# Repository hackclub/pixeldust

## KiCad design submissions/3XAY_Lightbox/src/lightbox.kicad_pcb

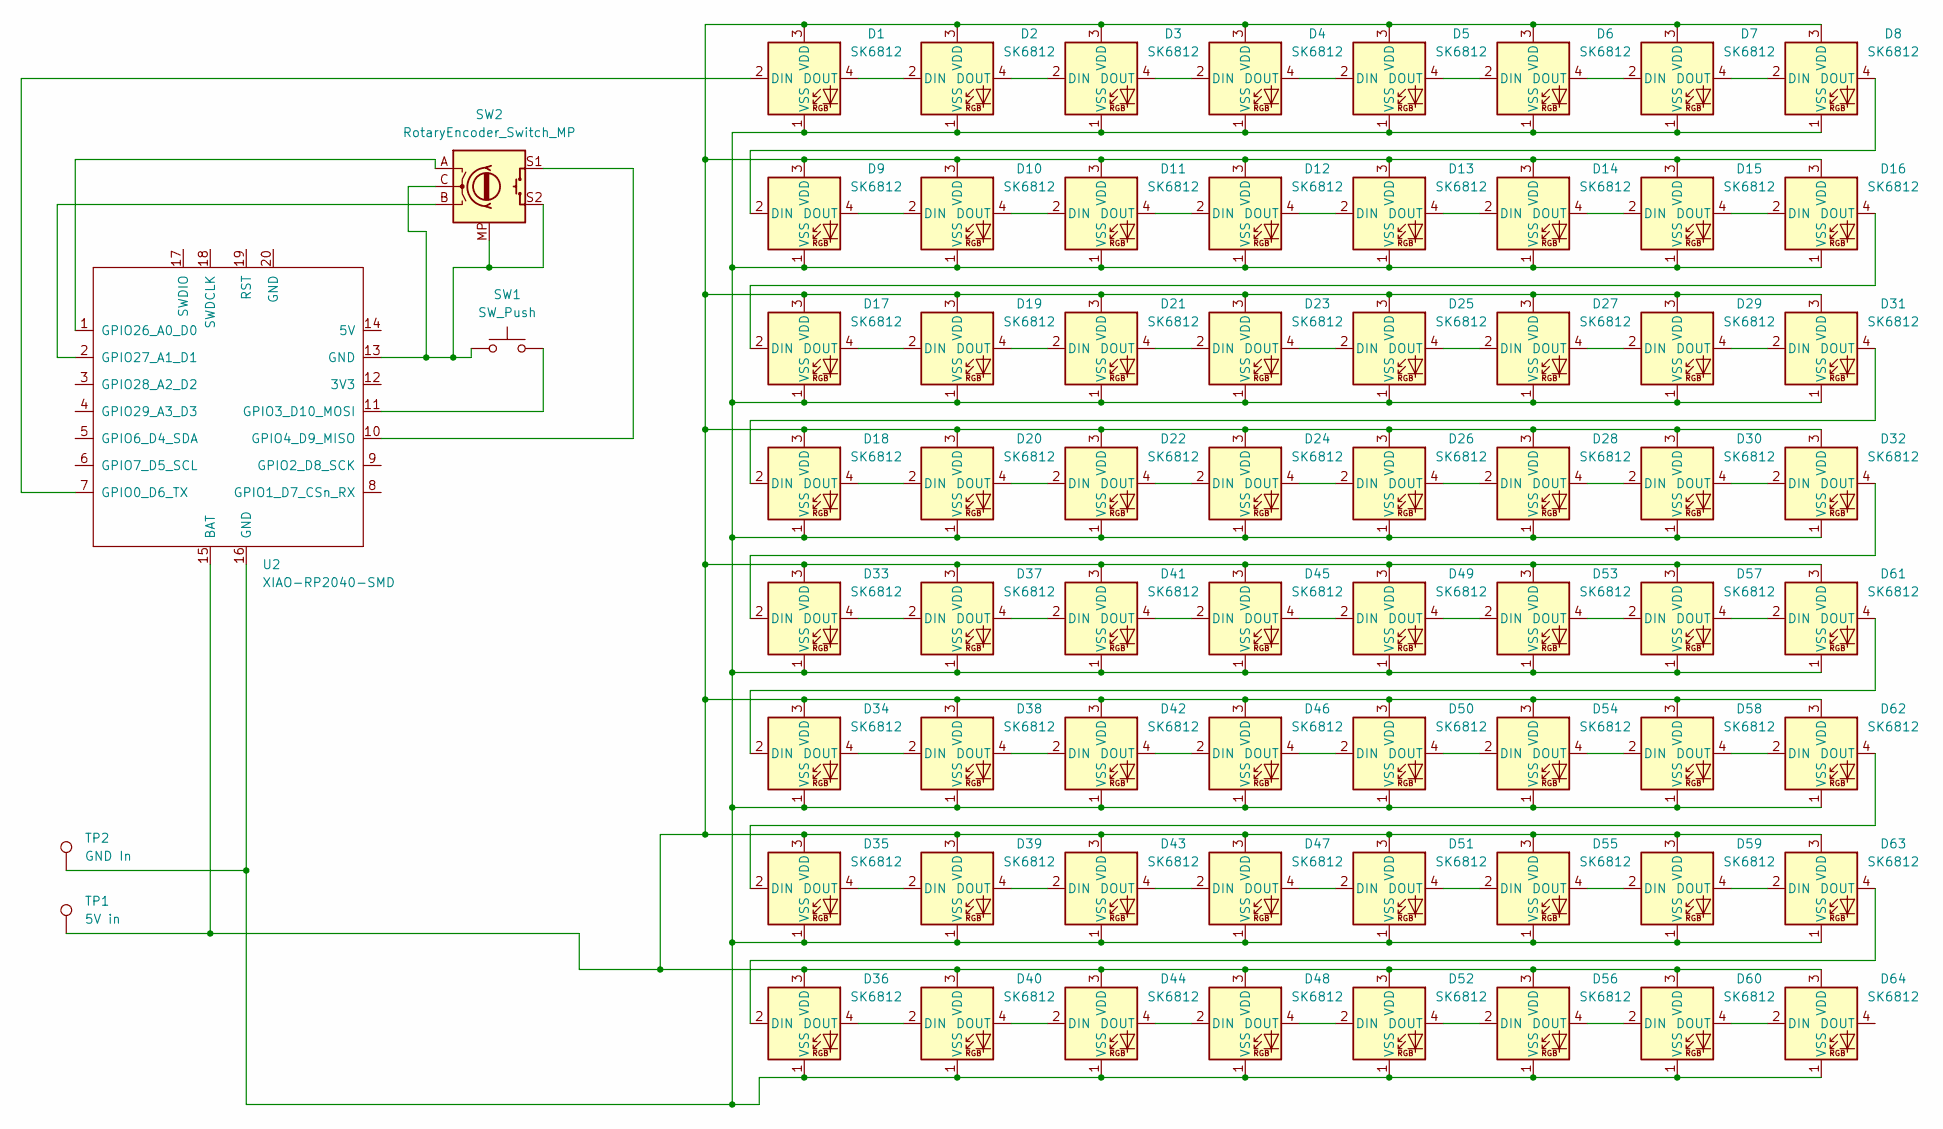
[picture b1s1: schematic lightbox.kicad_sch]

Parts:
D1, D2, D3, D4, D5, D6, D7, D8, D9, D10, D11, D12, D13, D14, D15, D16, D17, D18, D19, D20, D21, D22, D23, D24, D25, D26, D27, D28, D29, D30, D31, D32, D33, D34, D35, D36, D37, D38, D39, D40, D41, D42, D43, D44, D45, D46, D47, D48, D49, D50, D51, D52, D53, D54, D55, D56, D57, D58, D59, D60, D61, D62, D63, D64: SK6812; LED_SK6812_PLCC4_5.0x5.0mm_P3.2mm
SW1: SW_Push; SW_Cherry_MX_1.00u_PCB
SW2: RotaryEncoder_Switch_MP; RotaryEncoder_Alps_EC11E-Switch_Vertical_H20mm
TP1: 5V in; TestPoint_Pad_D3.0mm
TP2: GND In; TestPoint_Pad_D3.0mm
U2: XIAO-RP2040-SMD

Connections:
unnamed: D1.2 (DIN), U2.7 (GPIO0_D6_TX)
unnamed: D1.4 (DOUT), D2.2 (DIN)
unnamed: D1.3 (VDD), D2.3 (VDD), D3.3 (VDD), D4.3 (VDD), D5.3 (VDD), D6.3 (VDD), D7.3 (VDD), D8.3 (VDD), D9.3 (VDD), D10.3 (VDD), D11.3 (VDD), D12.3 (VDD), D13.3 (VDD), D14.3 (VDD), D15.3 (VDD), D16.3 (VDD), D17.3 (VDD), D18.3 (VDD), D19.3 (VDD), D20.3 (VDD), D21.3 (VDD), D22.3 (VDD), D23.3 (VDD), D24.3 (VDD), D25.3 (VDD), D26.3 (VDD), D27.3 (VDD), D28.3 (VDD), D29.3 (VDD), D30.3 (VDD), D31.3 (VDD), D32.3 (VDD), D33.3 (VDD), D34.3 (VDD), D35.3 (VDD), D36.3 (VDD), D37.3 (VDD), D38.3 (VDD), D39.3 (VDD), D40.3 (VDD), D41.3 (VDD), D42.3 (VDD), D43.3 (VDD), D44.3 (VDD), D45.3 (VDD), D46.3 (VDD), D47.3 (VDD), D48.3 (VDD), D49.3 (VDD), D50.3 (VDD), D51.3 (VDD), D52.3 (VDD), D53.3 (VDD), D54.3 (VDD), D55.3 (VDD), D56.3 (VDD), D57.3 (VDD), D58.3 (VDD), D59.3 (VDD), D60.3 (VDD), D61.3 (VDD), D62.3 (VDD), D63.3 (VDD), D64.3 (VDD), TP1.1, U2.15 (BAT)
unnamed: D1.1 (VSS), D2.1 (VSS), D3.1 (VSS), D4.1 (VSS), D5.1 (VSS), D6.1 (VSS), D7.1 (VSS), D8.1 (VSS), D9.1 (VSS), D10.1 (VSS), D11.1 (VSS), D12.1 (VSS), D13.1 (VSS), D14.1 (VSS), D15.1 (VSS), D16.1 (VSS), D17.1 (VSS), D18.1 (VSS), D19.1 (VSS), D20.1 (VSS), D21.1 (VSS), D22.1 (VSS), D23.1 (VSS), D24.1 (VSS), D25.1 (VSS), D26.1 (VSS), D27.1 (VSS), D28.1 (VSS), D29.1 (VSS), D30.1 (VSS), D31.1 (VSS), D32.1 (VSS), D33.1 (VSS), D34.1 (VSS), D35.1 (VSS), D36.1 (VSS), D37.1 (VSS), D38.1 (VSS), D39.1 (VSS), D40.1 (VSS), D41.1 (VSS), D42.1 (VSS), D43.1 (VSS), D44.1 (VSS), D45.1 (VSS), D46.1 (VSS), D47.1 (VSS), D48.1 (VSS), D49.1 (VSS), D50.1 (VSS), D51.1 (VSS), D52.1 (VSS), D53.1 (VSS), D54.1 (VSS), D55.1 (VSS), D56.1 (VSS), D57.1 (VSS), D58.1 (VSS), D59.1 (VSS), D60.1 (VSS), D61.1 (VSS), D62.1 (VSS), D63.1 (VSS), D64.1 (VSS), TP2.1, U2.16 (GND)
unnamed: D2.4 (DOUT), D3.2 (DIN)
unnamed: D3.4 (DOUT), D4.2 (DIN)
unnamed: D4.4 (DOUT), D5.2 (DIN)
unnamed: D5.4 (DOUT), D6.2 (DIN)
unnamed: D6.4 (DOUT), D7.2 (DIN)
unnamed: D7.4 (DOUT), D8.2 (DIN)
unnamed: D8.4 (DOUT), D9.2 (DIN)
unnamed: D9.4 (DOUT), D10.2 (DIN)
unnamed: D10.4 (DOUT), D11.2 (DIN)
unnamed: D11.4 (DOUT), D12.2 (DIN)
unnamed: D12.4 (DOUT), D13.2 (DIN)
unnamed: D13.4 (DOUT), D14.2 (DIN)
unnamed: D14.4 (DOUT), D15.2 (DIN)
unnamed: D15.4 (DOUT), D16.2 (DIN)
unnamed: D16.4 (DOUT), D17.2 (DIN)
unnamed: D17.4 (DOUT), D19.2 (DIN)
unnamed: D18.2 (DIN), D31.4 (DOUT)
unnamed: D18.4 (DOUT), D20.2 (DIN)
unnamed: D19.4 (DOUT), D21.2 (DIN)
unnamed: D20.4 (DOUT), D22.2 (DIN)
unnamed: D21.4 (DOUT), D23.2 (DIN)
unnamed: D22.4 (DOUT), D24.2 (DIN)
unnamed: D23.4 (DOUT), D25.2 (DIN)
unnamed: D24.4 (DOUT), D26.2 (DIN)
unnamed: D25.4 (DOUT), D27.2 (DIN)
unnamed: D26.4 (DOUT), D28.2 (DIN)
unnamed: D27.4 (DOUT), D29.2 (DIN)
unnamed: D28.4 (DOUT), D30.2 (DIN)
unnamed: D29.4 (DOUT), D31.2 (DIN)
unnamed: D30.4 (DOUT), D32.2 (DIN)
unnamed: D32.4 (DOUT), D33.2 (DIN)
unnamed: D33.4 (DOUT), D37.2 (DIN)
unnamed: D34.2 (DIN), D61.4 (DOUT)
unnamed: D34.4 (DOUT), D38.2 (DIN)
unnamed: D35.2 (DIN), D62.4 (DOUT)
unnamed: D35.4 (DOUT), D39.2 (DIN)
unnamed: D36.2 (DIN), D63.4 (DOUT)
unnamed: D36.4 (DOUT), D40.2 (DIN)
unnamed: D37.4 (DOUT), D41.2 (DIN)
unnamed: D38.4 (DOUT), D42.2 (DIN)
unnamed: D39.4 (DOUT), D43.2 (DIN)
unnamed: D40.4 (DOUT), D44.2 (DIN)
unnamed: D41.4 (DOUT), D45.2 (DIN)
unnamed: D42.4 (DOUT), D46.2 (DIN)
unnamed: D43.4 (DOUT), D47.2 (DIN)
unnamed: D44.4 (DOUT), D48.2 (DIN)
unnamed: D45.4 (DOUT), D49.2 (DIN)
unnamed: D46.4 (DOUT), D50.2 (DIN)
unnamed: D47.4 (DOUT), D51.2 (DIN)
unnamed: D48.4 (DOUT), D52.2 (DIN)
unnamed: D49.4 (DOUT), D53.2 (DIN)
unnamed: D50.4 (DOUT), D54.2 (DIN)
unnamed: D51.4 (DOUT), D55.2 (DIN)
unnamed: D52.4 (DOUT), D56.2 (DIN)
unnamed: D53.4 (DOUT), D57.2 (DIN)
unnamed: D54.4 (DOUT), D58.2 (DIN)
unnamed: D55.4 (DOUT), D59.2 (DIN)
unnamed: D56.4 (DOUT), D60.2 (DIN)
unnamed: D57.4 (DOUT), D61.2 (DIN)
unnamed: D58.4 (DOUT), D62.2 (DIN)
unnamed: D59.4 (DOUT), D63.2 (DIN)
unnamed: D60.4 (DOUT), D64.2 (DIN)
unnamed: SW1.1, SW2.C, SW2.MP, SW2.S2, U2.13 (GND)
unnamed: SW1.2, U2.11 (GPIO3_D10_MOSI)
unnamed: SW2.S1, U2.10 (GPIO4_D9_MISO)
unnamed: SW2.A, U2.1 (GPIO26_A0_D0)
unnamed: SW2.B, U2.2 (GPIO27_A1_D1)

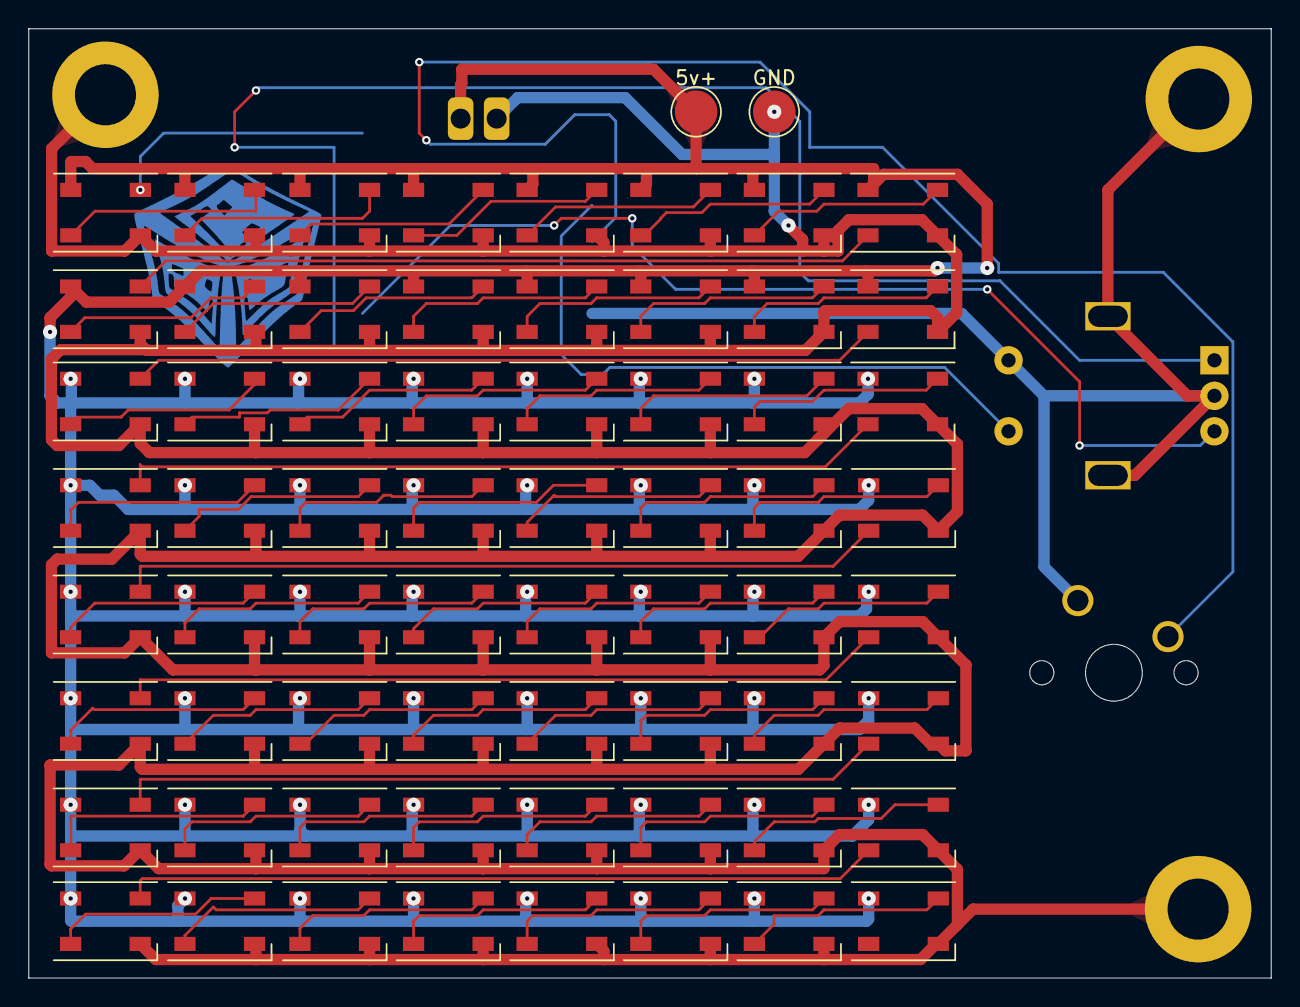
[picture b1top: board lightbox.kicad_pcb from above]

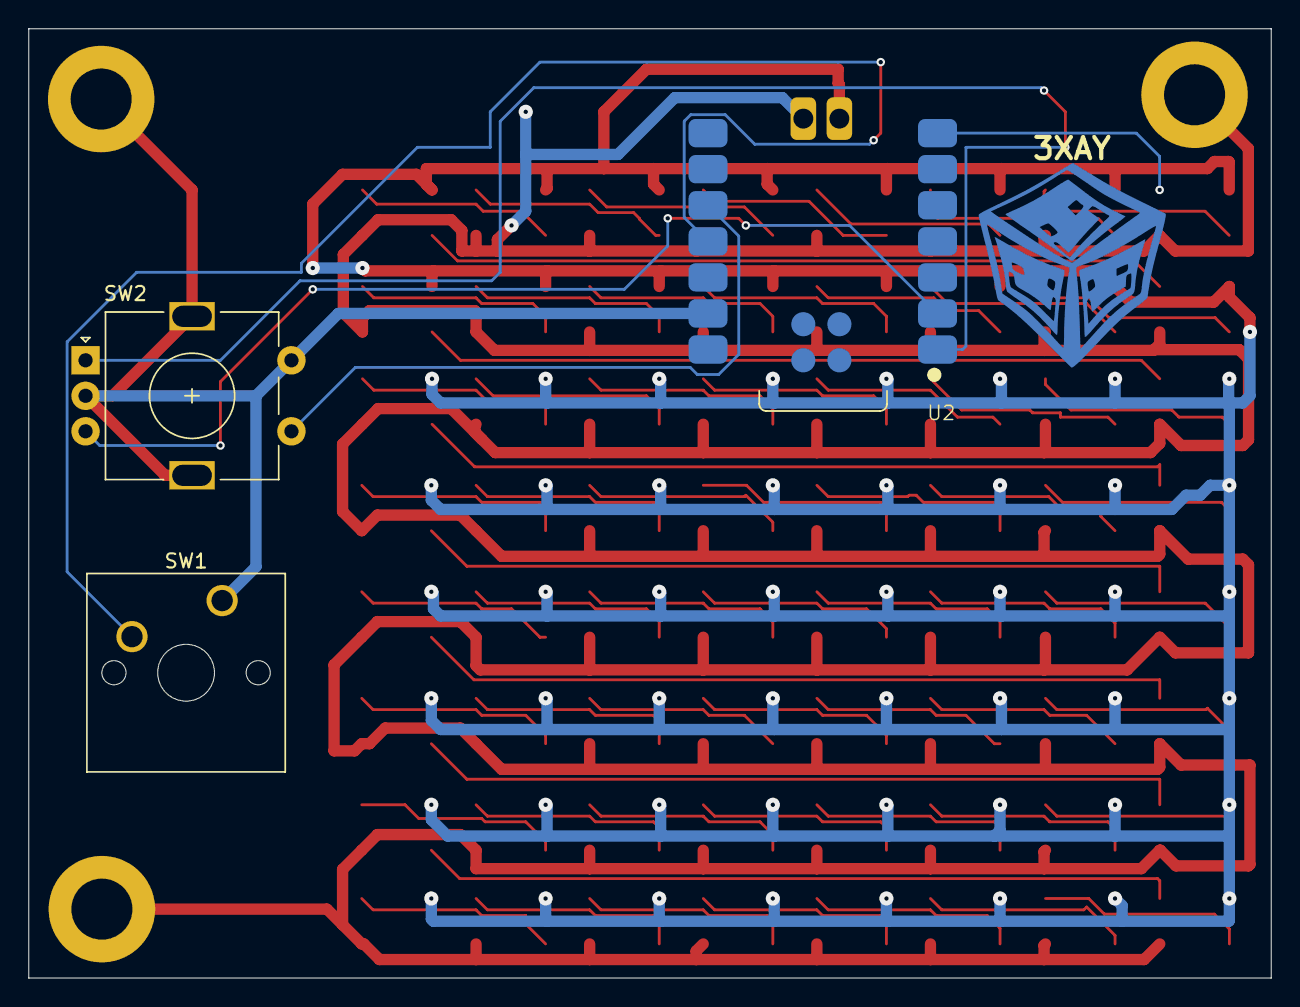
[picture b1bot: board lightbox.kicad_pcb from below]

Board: 2 copper layers, 87.5 x 66.8 mm, 69 parts (3 on the bottom side), 71 nets.

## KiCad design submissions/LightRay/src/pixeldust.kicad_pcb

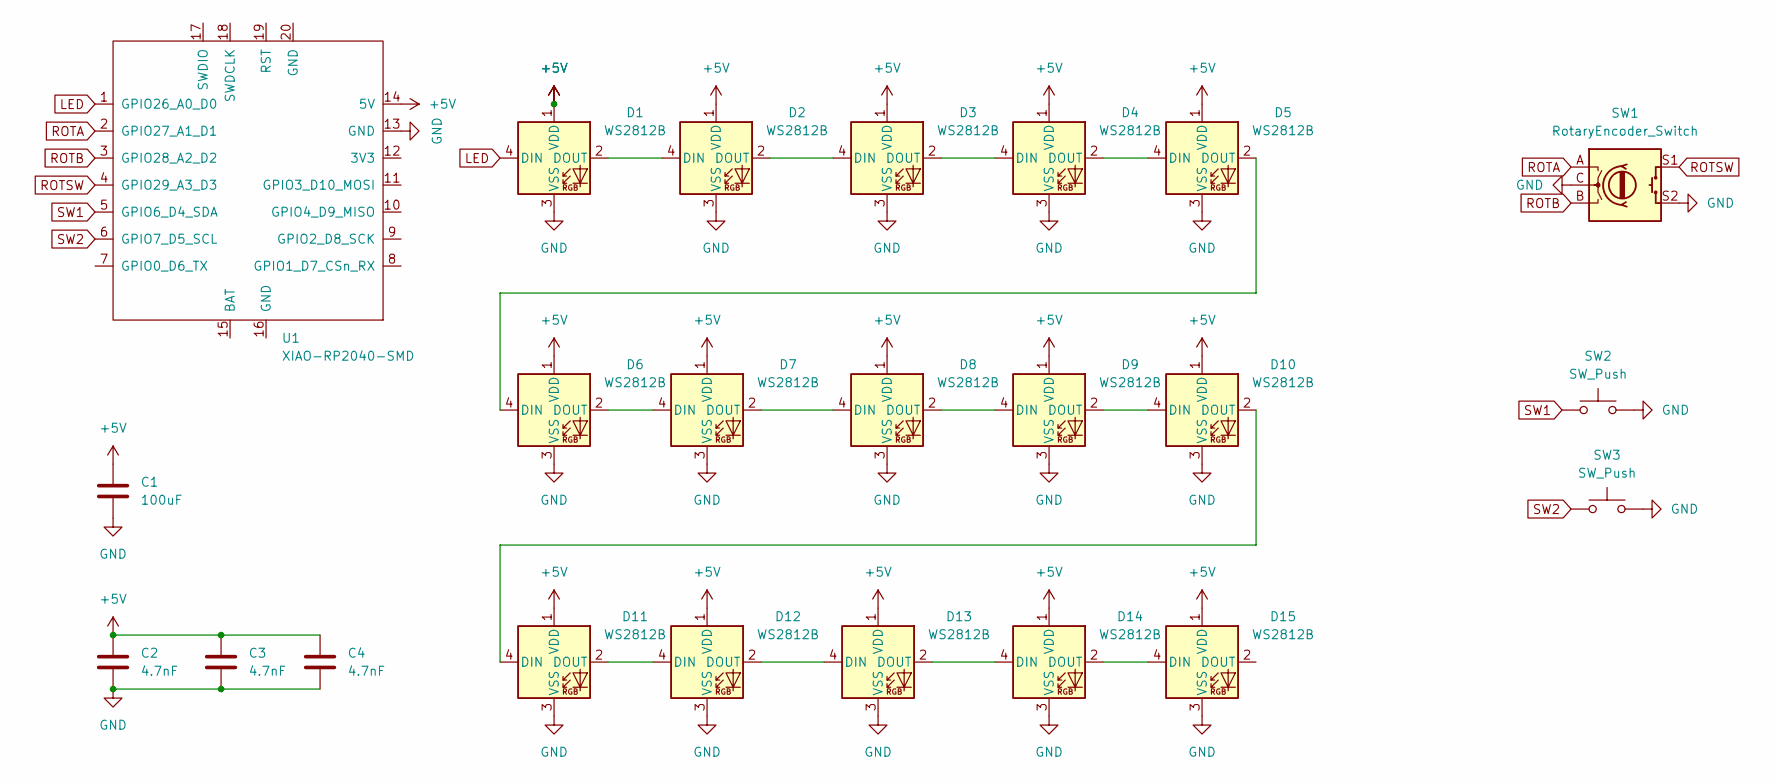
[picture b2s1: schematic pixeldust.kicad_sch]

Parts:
C1: 100uF; C_1210_3225Metric_Pad1.33x2.70mm_HandSolder
C2, C3, C4: 4.7nF; C_1206_3216Metric_Pad1.33x1.80mm_HandSolder
D1, D2, D3, D4, D5, D6, D7, D8, D9, D10, D11, D12, D13, D14, D15: WS2812B; LED_WS2812B_PLCC4_5.0x5.0mm_P3.2mm
SW1: RotaryEncoder_Switch; RotaryEncoder_Alps_EC11E-Switch_Vertical_H20mm
SW2, SW3: SW_Push; SW_Cherry_MX_1.00u_PCB
U1: XIAO-RP2040-SMD

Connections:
+5V: C1.1, C2.1, C3.1, C4.1, D1.1 (VDD), D2.1 (VDD), D3.1 (VDD), D4.1 (VDD), D5.1 (VDD), D6.1 (VDD), D7.1 (VDD), D8.1 (VDD), D9.1 (VDD), D10.1 (VDD), D11.1 (VDD), D12.1 (VDD), D13.1 (VDD), D14.1 (VDD), D15.1 (VDD), U1.14 (5V)
GND: C1.2, C2.2, C3.2, C4.2, D1.3 (VSS), D2.3 (VSS), D3.3 (VSS), D4.3 (VSS), D5.3 (VSS), D6.3 (VSS), D7.3 (VSS), D8.3 (VSS), D9.3 (VSS), D10.3 (VSS), D11.3 (VSS), D12.3 (VSS), D13.3 (VSS), D14.3 (VSS), D15.3 (VSS), SW1.C, SW1.S2, SW2.2, SW3.2, U1.13 (GND)
LED: D1.4 (DIN), U1.1 (GPIO26_A0_D0)
unnamed: D1.2 (DOUT), D2.4 (DIN)
unnamed: D2.2 (DOUT), D3.4 (DIN)
unnamed: D3.2 (DOUT), D4.4 (DIN)
unnamed: D4.2 (DOUT), D5.4 (DIN)
unnamed: D5.2 (DOUT), D6.4 (DIN)
unnamed: D6.2 (DOUT), D7.4 (DIN)
unnamed: D7.2 (DOUT), D8.4 (DIN)
unnamed: D8.2 (DOUT), D9.4 (DIN)
unnamed: D9.2 (DOUT), D10.4 (DIN)
unnamed: D10.2 (DOUT), D11.4 (DIN)
unnamed: D11.2 (DOUT), D12.4 (DIN)
unnamed: D12.2 (DOUT), D13.4 (DIN)
unnamed: D13.2 (DOUT), D14.4 (DIN)
unnamed: D14.2 (DOUT), D15.4 (DIN)
ROTA: SW1.A, U1.2 (GPIO27_A1_D1)
ROTB: SW1.B, U1.3 (GPIO28_A2_D2)
ROTSW: SW1.S1, U1.4 (GPIO29_A3_D3)
SW1: SW2.1, U1.5 (GPIO6_D4_SDA)
SW2: SW3.1, U1.6 (GPIO7_D5_SCL)

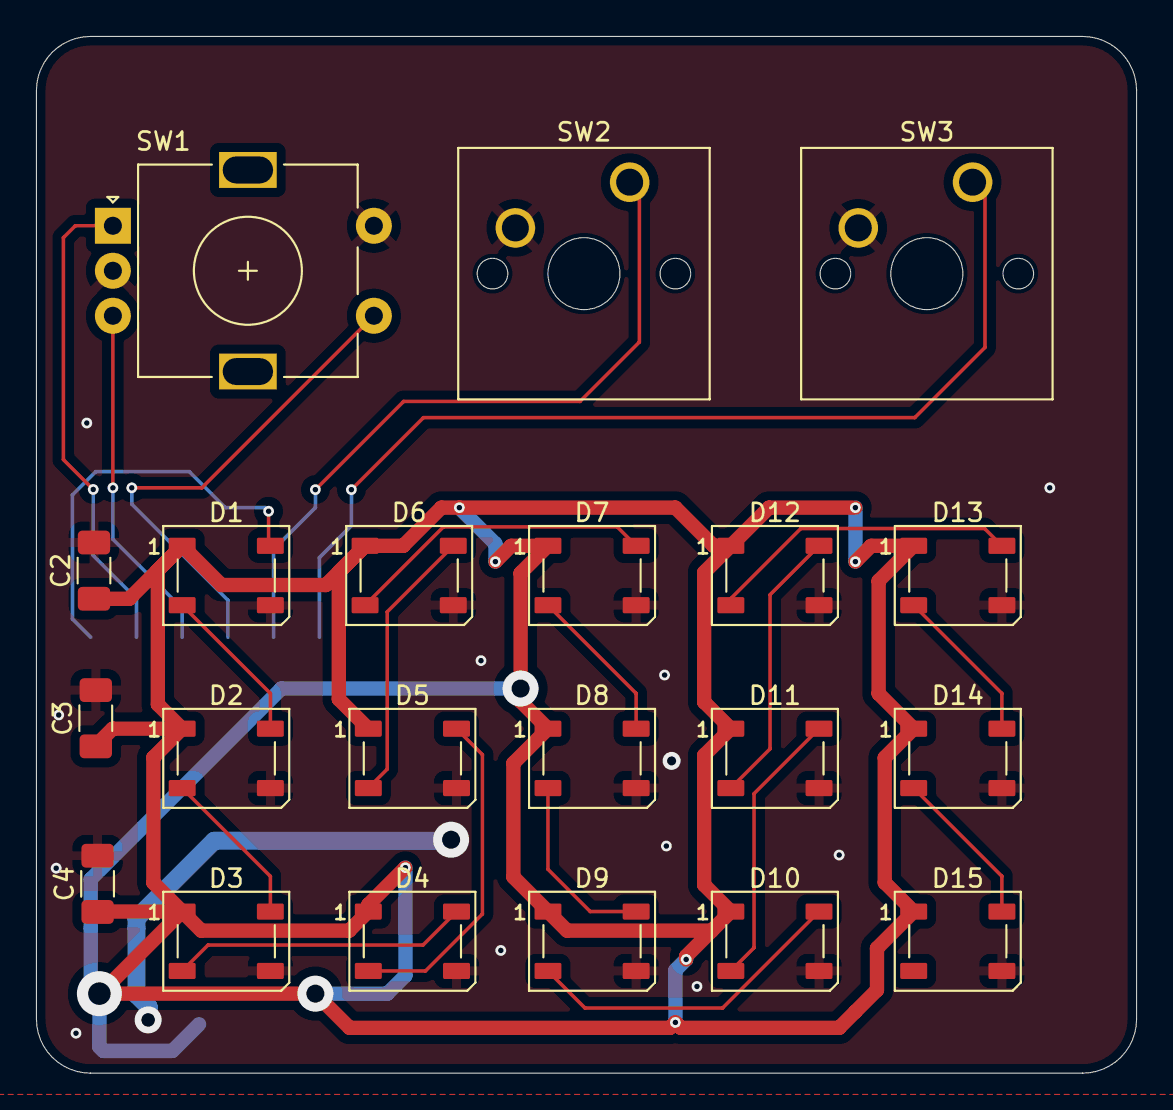
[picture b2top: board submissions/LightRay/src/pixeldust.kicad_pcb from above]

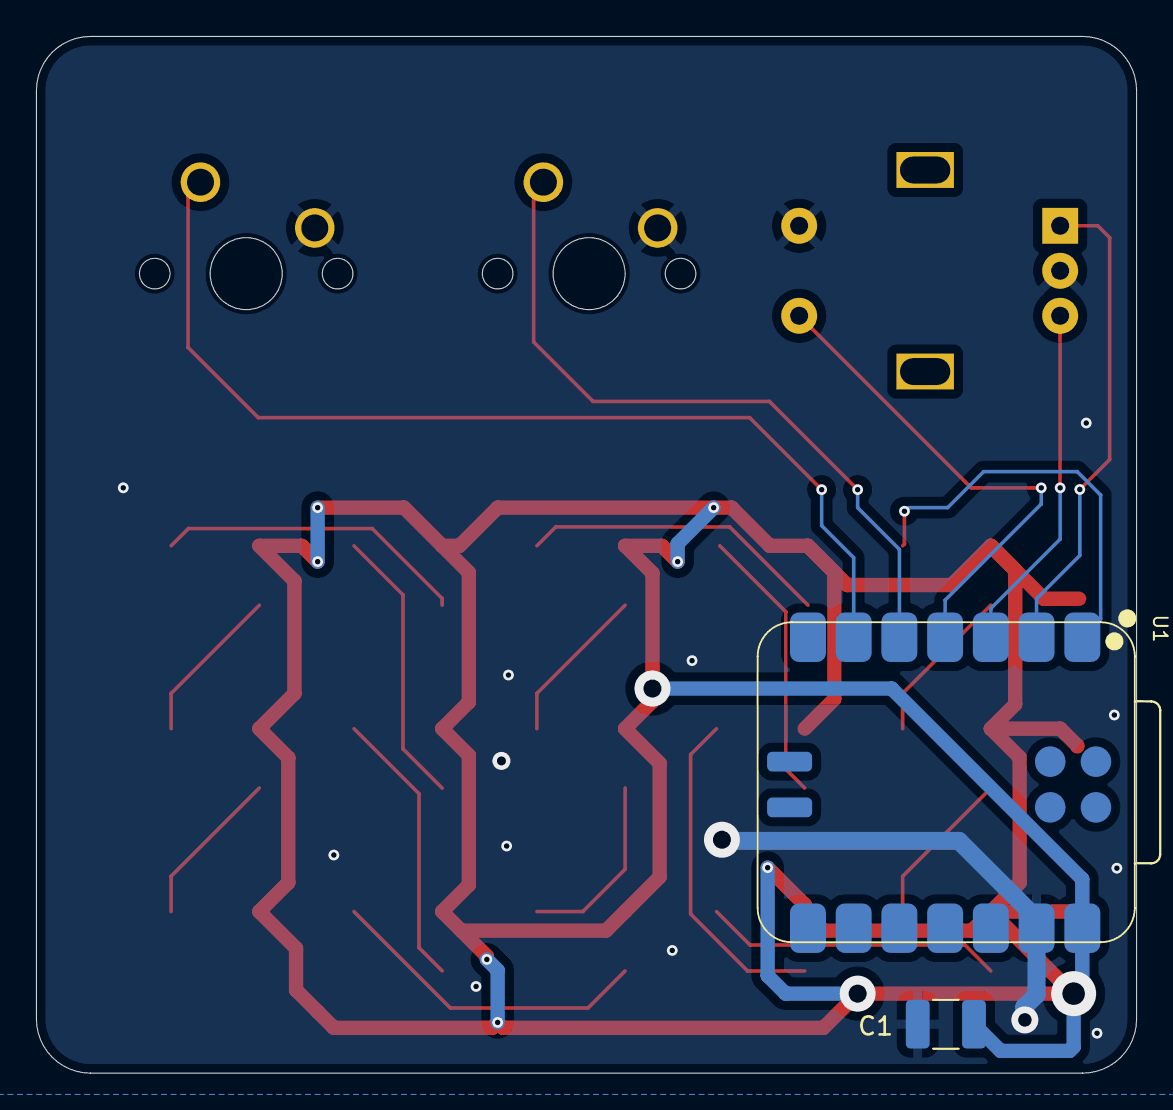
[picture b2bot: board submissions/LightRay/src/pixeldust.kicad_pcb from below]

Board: 2 copper layers, 61.1 x 57.6 mm, 23 parts (2 on the bottom side), 22 nets.

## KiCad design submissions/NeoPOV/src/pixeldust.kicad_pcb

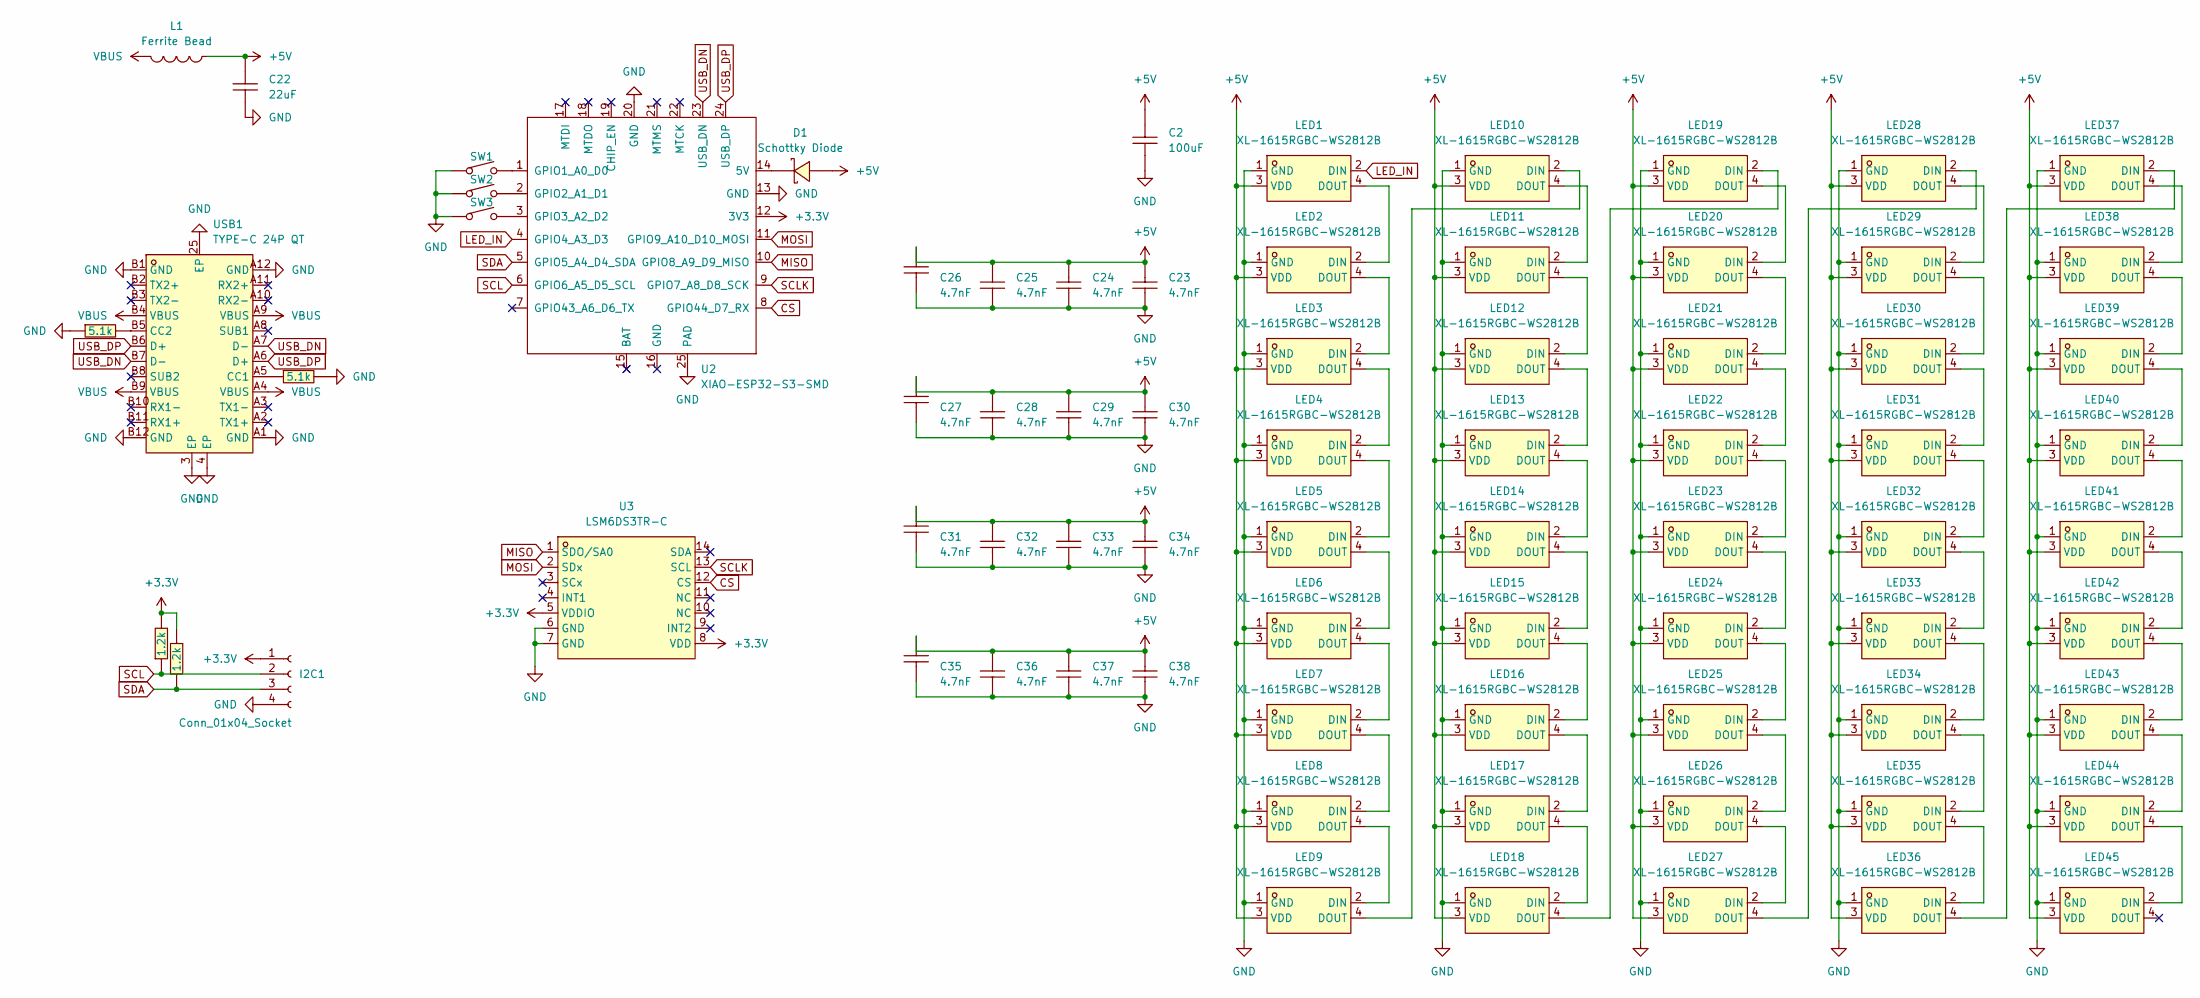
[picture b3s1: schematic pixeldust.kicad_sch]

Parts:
C2: 100uF; C1206; LCSC Part C7432784
C22: 22uF; C0603; LCSC Part C59461
C23, C24, C25, C26, C27, C28, C29, C30, C31, C32, C33, C34, C35, C36, C37, C38: 4.7nF; C0603; LCSC Part C106218
D1: Schottky Diode; SMA_L4.3-W2.6-LS5.2-RD; LCSC Part C8678
I2C1: Conn_01x04_Socket; PinSocket_1x04_P1.27mm_Vertical
L1: Ferrite Bead; L0603; LCSC Part C14709
LED1, LED2, LED3, LED4, LED5, LED6, LED7, LED8, LED9, LED10, LED11, LED12, LED13, LED14, LED15, LED16, LED17, LED18, LED19, LED20, LED21, LED22, LED23, LED24, LED25, LED26, LED27, LED28, LED29, LED30, LED31, LED32, LED33, LED34, LED35, LED36, LED37, LED38, LED39, LED40, LED41, LED42, LED43, LED44, LED45: XL-1615RGBC-WS2812B; LED-SMD_4P-L1.6-W1.5_XL-1615RGBC-WS2812B-1; LCSC Part C5349954
R3, R4: 1.2k; R0603; LCSC Part C114605
R5, R6: 5.1k; R0603; LCSC Part C23186
SW1, SW2, SW3: TS342A2P-WZ; SW-SMD_L4.0-W2.9-LS5.0; LCSC Part C557591
U2: XIAO-ESP32-S3-SMD; XIAO-ESP32S3-SMD
U3: LSM6DS3TR-C; LGA-14_L3.0-W2.5-P0.50-TL; LCSC Part C967633
USB1: TYPE-C 24P QT; USB-C-SMD_TYPE-C-24P-QT; LCSC Part C2681555

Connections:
+3.3V: I2C1.1, R3.2, R4.2, U2.12 (3V3), U3.5 (VDDIO), U3.8 (VDD)
+5V: C2.2, C22.2, C23.2, C24.2, C25.2, C26.2, C27.2, C28.2, C29.2, C30.2, C31.2, C32.2, C33.2, C34.2, C35.2, C36.2, C37.2, C38.2, D1.2 (A), L1.2, LED1.3 (VDD), LED2.3 (VDD), LED3.3 (VDD), LED4.3 (VDD), LED5.3 (VDD), LED6.3 (VDD), LED7.3 (VDD), LED8.3 (VDD), LED9.3 (VDD), LED10.3 (VDD), LED11.3 (VDD), LED12.3 (VDD), LED13.3 (VDD), LED14.3 (VDD), LED15.3 (VDD), LED16.3 (VDD), LED17.3 (VDD), LED18.3 (VDD), LED19.3 (VDD), LED20.3 (VDD), LED21.3 (VDD), LED22.3 (VDD), LED23.3 (VDD), LED24.3 (VDD), LED25.3 (VDD), LED26.3 (VDD), LED27.3 (VDD), LED28.3 (VDD), LED29.3 (VDD), LED30.3 (VDD), LED31.3 (VDD), LED32.3 (VDD), LED33.3 (VDD), LED34.3 (VDD), LED35.3 (VDD), LED36.3 (VDD), LED37.3 (VDD), LED38.3 (VDD), LED39.3 (VDD), LED40.3 (VDD), LED41.3 (VDD), LED42.3 (VDD), LED43.3 (VDD), LED44.3 (VDD), LED45.3 (VDD)
CS: U2.8 (GPIO44_D7_RX), U3.12 (CS)
GND: C2.1, C22.1, C23.1, C24.1, C25.1, C26.1, C27.1, C28.1, C29.1, C30.1, C31.1, C32.1, C33.1, C34.1, C35.1, C36.1, C37.1, C38.1, I2C1.4, LED1.1 (GND), LED2.1 (GND), LED3.1 (GND), LED4.1 (GND), LED5.1 (GND), LED6.1 (GND), LED7.1 (GND), LED8.1 (GND), LED9.1 (GND), LED10.1 (GND), LED11.1 (GND), LED12.1 (GND), LED13.1 (GND), LED14.1 (GND), LED15.1 (GND), LED16.1 (GND), LED17.1 (GND), LED18.1 (GND), LED19.1 (GND), LED20.1 (GND), LED21.1 (GND), LED22.1 (GND), LED23.1 (GND), LED24.1 (GND), LED25.1 (GND), LED26.1 (GND), LED27.1 (GND), LED28.1 (GND), LED29.1 (GND), LED30.1 (GND), LED31.1 (GND), LED32.1 (GND), LED33.1 (GND), LED34.1 (GND), LED35.1 (GND), LED36.1 (GND), LED37.1 (GND), LED38.1 (GND), LED39.1 (GND), LED40.1 (GND), LED41.1 (GND), LED42.1 (GND), LED43.1 (GND), LED44.1 (GND), LED45.1 (GND), R5.2, R6.1, SW1.1, SW2.1, SW3.1, U2.13 (GND), U2.20 (GND), U2.25 (PAD), U3.6 (GND), U3.7 (GND), USB1.3 (EP), USB1.4 (EP), USB1.25 (EP), USB1.A1 (GND), USB1.A12 (GND), USB1.B1 (GND), USB1.B12 (GND)
LED_IN: LED1.2 (DIN), U2.4 (GPIO4_A3_D3)
MISO: U2.10 (GPIO8_A9_D9_MISO), U3.1 (SDO/SA0)
MOSI: U2.11 (GPIO9_A10_D10_MOSI), U3.2 (SDx)
unnamed: D1.1 (K), U2.14 (5V)
unnamed: LED1.4 (DOUT), LED2.2 (DIN)
unnamed: LED2.4 (DOUT), LED3.2 (DIN)
unnamed: LED3.4 (DOUT), LED4.2 (DIN)
unnamed: LED4.4 (DOUT), LED5.2 (DIN)
unnamed: LED5.4 (DOUT), LED6.2 (DIN)
unnamed: LED6.4 (DOUT), LED7.2 (DIN)
unnamed: LED7.4 (DOUT), LED8.2 (DIN)
unnamed: LED8.4 (DOUT), LED9.2 (DIN)
unnamed: LED9.4 (DOUT), LED10.2 (DIN)
unnamed: LED10.4 (DOUT), LED11.2 (DIN)
unnamed: LED11.4 (DOUT), LED12.2 (DIN)
unnamed: LED12.4 (DOUT), LED13.2 (DIN)
unnamed: LED13.4 (DOUT), LED14.2 (DIN)
unnamed: LED14.4 (DOUT), LED15.2 (DIN)
unnamed: LED15.4 (DOUT), LED16.2 (DIN)
unnamed: LED16.4 (DOUT), LED17.2 (DIN)
unnamed: LED17.4 (DOUT), LED18.2 (DIN)
unnamed: LED18.4 (DOUT), LED19.2 (DIN)
unnamed: LED19.4 (DOUT), LED20.2 (DIN)
unnamed: LED20.4 (DOUT), LED21.2 (DIN)
unnamed: LED21.4 (DOUT), LED22.2 (DIN)
unnamed: LED22.4 (DOUT), LED23.2 (DIN)
unnamed: LED23.4 (DOUT), LED24.2 (DIN)
unnamed: LED24.4 (DOUT), LED25.2 (DIN)
unnamed: LED25.4 (DOUT), LED26.2 (DIN)
unnamed: LED26.4 (DOUT), LED27.2 (DIN)
unnamed: LED27.4 (DOUT), LED28.2 (DIN)
unnamed: LED28.4 (DOUT), LED29.2 (DIN)
unnamed: LED29.4 (DOUT), LED30.2 (DIN)
unnamed: LED30.4 (DOUT), LED31.2 (DIN)
unnamed: LED31.4 (DOUT), LED32.2 (DIN)
unnamed: LED32.4 (DOUT), LED33.2 (DIN)
unnamed: LED33.4 (DOUT), LED34.2 (DIN)
unnamed: LED34.4 (DOUT), LED35.2 (DIN)
unnamed: LED35.4 (DOUT), LED36.2 (DIN)
unnamed: LED36.4 (DOUT), LED37.2 (DIN)
unnamed: LED37.4 (DOUT), LED38.2 (DIN)
unnamed: LED38.4 (DOUT), LED39.2 (DIN)
unnamed: LED39.4 (DOUT), LED40.2 (DIN)
unnamed: LED40.4 (DOUT), LED41.2 (DIN)
unnamed: LED41.4 (DOUT), LED42.2 (DIN)
unnamed: LED42.4 (DOUT), LED43.2 (DIN)
unnamed: LED43.4 (DOUT), LED44.2 (DIN)
unnamed: LED44.4 (DOUT), LED45.2 (DIN)
unnamed: SW1.2, U2.1 (GPIO1_A0_D0)
unnamed: SW2.2, U2.2 (GPIO2_A1_D1)
unnamed: SW3.2, U2.3 (GPIO3_A2_D2)
unnamed: R5.1, USB1.A5 (CC1)
unnamed: R6.2, USB1.B5 (CC2)
SCL: I2C1.2, R3.1, U2.6 (GPIO6_A5_D5_SCL)
SCLK: U2.9 (GPIO7_A8_D8_SCK), U3.13 (SCL)
SDA: I2C1.3, R4.1, U2.5 (GPIO5_A4_D4_SDA)
USB_DN: U2.23 (USB_DN), USB1.A7 (D-), USB1.B7 (D-)
USB_DP: U2.24 (USB_DP), USB1.A6 (D+), USB1.B6 (D+)
VBUS: L1.1, USB1.A4 (VBUS), USB1.A9 (VBUS), USB1.B4 (VBUS), USB1.B9 (VBUS)

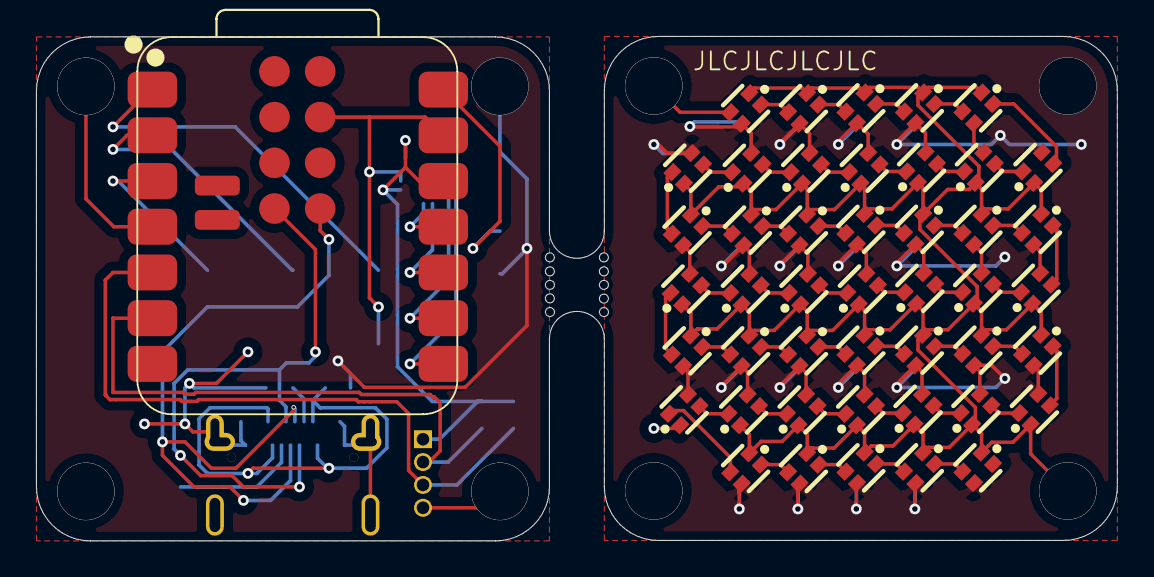
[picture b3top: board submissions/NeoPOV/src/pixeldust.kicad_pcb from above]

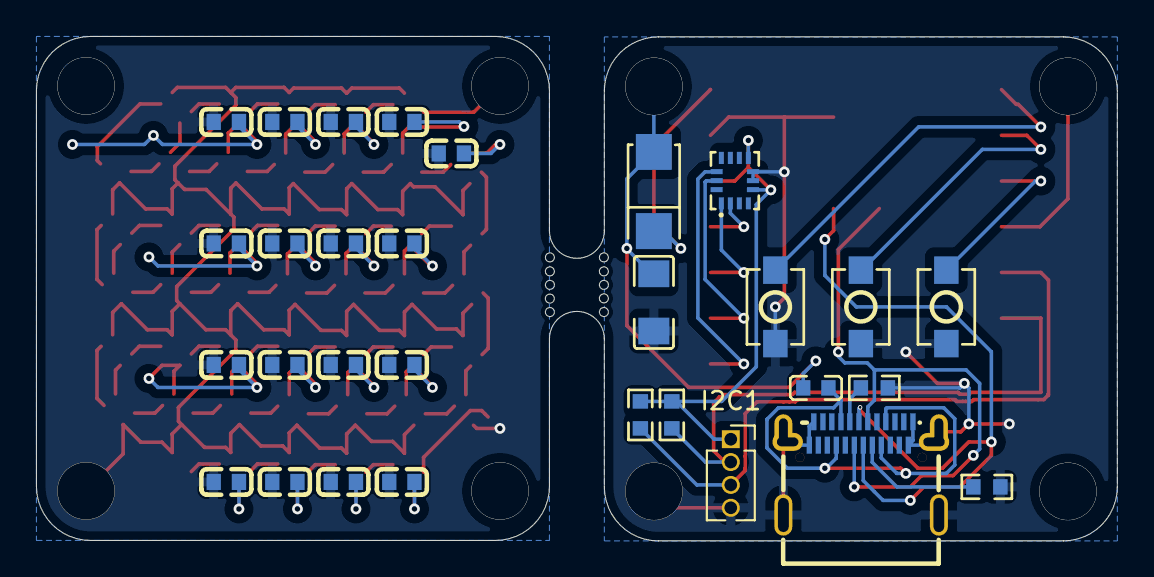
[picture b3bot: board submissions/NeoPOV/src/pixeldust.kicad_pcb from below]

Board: 2 copper layers, 60.0 x 28.0 mm, 76 parts (30 on the bottom side), 63 nets.
